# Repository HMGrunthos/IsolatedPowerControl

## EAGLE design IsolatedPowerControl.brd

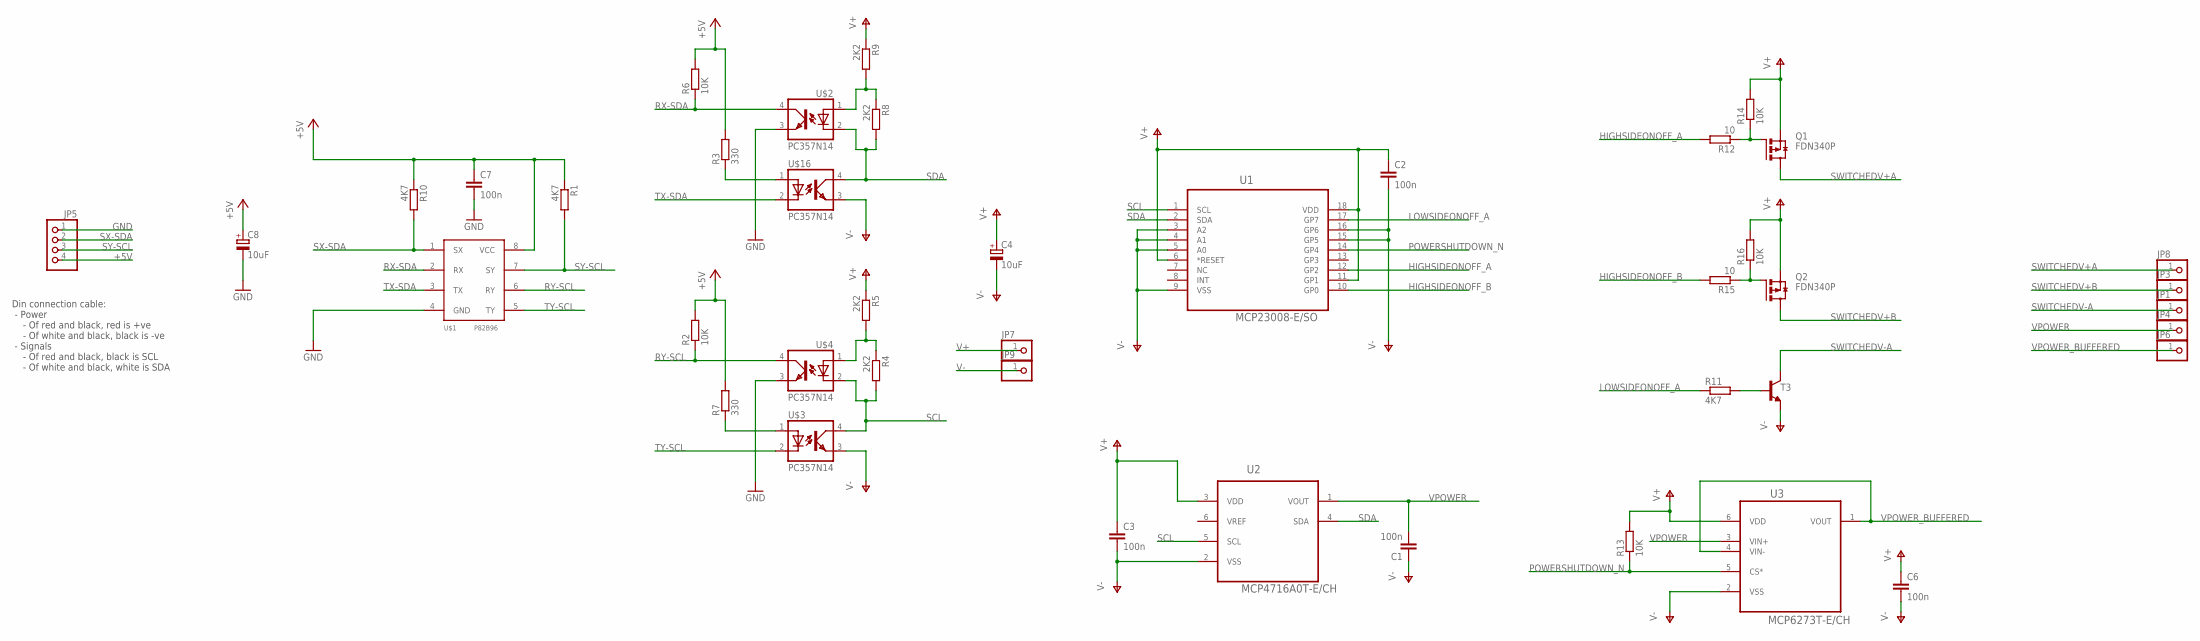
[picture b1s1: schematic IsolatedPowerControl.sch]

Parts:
C1, C2, C3, C6, C7: 100n; C1206K
C4, C8: 10uF; E2-5
JP1, JP3, JP4, JP6, JP7, JP8, JP9: PINHD-1X1LARGEPAD; 1X01-LARGEPAD
JP5: PINHD-1X4; 1X04
Q1, Q2: FDN340P; SUPER-SOT3
R1, R10, R11: 4K7; R0402
R2, R6, R13, R14, R16: 10K; R0805
R3, R7: 330; R0402
R4, R5, R8, R9: 2K2; R0402
R12, R15: 10; R0603
T3: MMBTA42LT1-NPN-SOT23-BEC; SOT23-BEC
U1: MCP23008-E/SO; SOIC127P1030X265-18N
U2: MCP4716A0T-E/CH; SOT95P270X145-6N
U3: MCP6273T-E/CH; SOT95P280X145-6N
U$1: P82B96; SOIC8
U$2, U$3, U$4, U$16: PC357N14; MINI-FLAT-4-DS

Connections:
+5V: C7.1, C8.+, JP5.4, R1.1, R2.2, R3.2, R6.2, R7.2, R10.1, U$1.8 (VCC)
GND: C7.2, C8.-, JP5.1, U$1.4 (GND), U$2.3 (EMIT), U$4.3 (EMIT)
HIGHSIDEONOFF_A: R12.2, U1.12 (GP2)
HIGHSIDEONOFF_B: R15.2, U1.10 (GP0)
LOWSIDEONOFF_A: R11.1, U1.17 (GP7)
unnamed: R3.1, U$16.1 (A)
unnamed: R8.1, R9.2, U$2.1 (A)
unnamed: R7.1, U$3.1 (A)
unnamed: R4.1, R5.2, U$4.1 (A)
unnamed: R11.2, T3.B
unnamed: Q2.1 (G), R15.1, R16.1
unnamed: Q1.1 (G), R12.1, R14.1
POWERSHUTDOWN_N: R13.1, U1.14 (GP4), U3.5 (CS*)
RX-SDA: R6.1, U$1.2 (RX), U$2.4 (COL)
RY-SCL: R2.1, U$1.6 (RY), U$4.4 (COL)
SCL: R4.2, U1.1 (SCL), U2.5 (SCL), U$3.4 (COL), U$4.2 (C)
SDA: R8.2, U1.2 (SDA), U2.4 (SDA), U$2.2 (C), U$16.4 (COL)
SWITCHEDV+A: JP8.1, Q1.3 (D)
SWITCHEDV+B: JP3.1, Q2.3 (D)
SWITCHEDV-A: JP1.1, T3.C
SX-SDA: JP5.2, R10.2, U$1.1 (SX)
SY-SCL: JP5.3, R1.2, U$1.7 (SY)
TX-SDA: U$1.3 (TX), U$16.2 (C)
TY-SCL: U$1.5 (TY), U$3.2 (C)
V+: C2.1, C3.1, C4.+, C6.1, JP7.1, Q1.2 (S), Q2.2 (S), R5.1, R9.1, R13.2, R14.2, R16.2, U1.6 (*RESET), U1.11 (GP1), U1.18 (VDD), U2.3 (VDD), U3.6 (VDD)
V-: C1.1, C2.2, C3.2, C4.-, C6.2, JP9.1, T3.E, U1.3 (A2), U1.4 (A1), U1.5 (A0), U1.9 (VSS), U1.15 (GP5), U1.16 (GP6), U2.2 (VSS), U3.2 (VSS), U$3.3 (EMIT), U$16.3 (EMIT)
VPOWER: C1.2, JP4.1, U2.1 (VOUT), U3.3 (VIN+)
VPOWER_BUFFERED: JP6.1, U3.1 (VOUT), U3.4 (VIN-)

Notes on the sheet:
Din connection cable: - Power - Of red and black, red is +ve - Of white and black, black is -ve - Signals - Of red and black, black is SCL - Of white and black, white is SDA

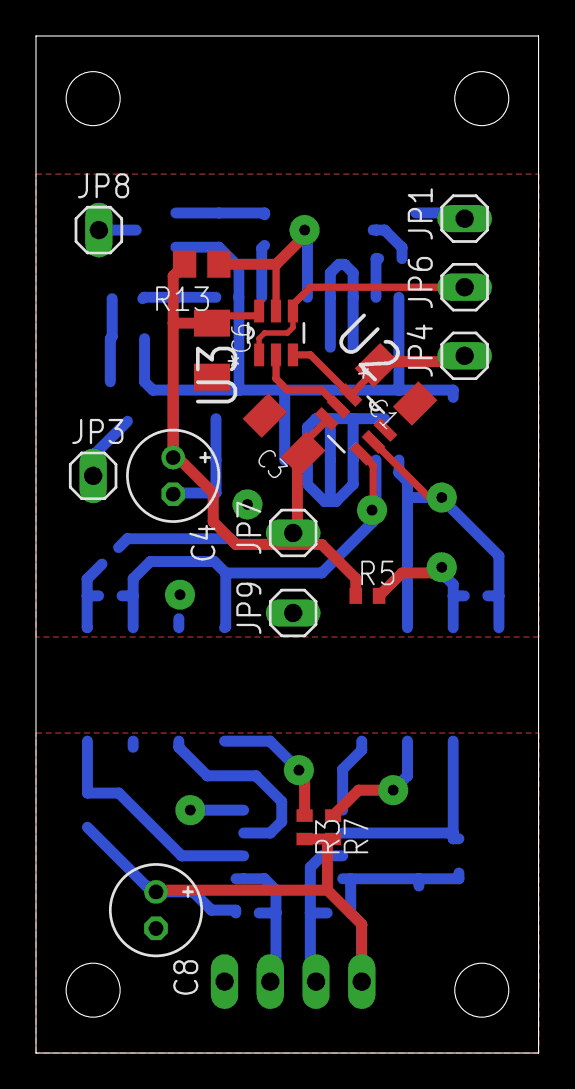
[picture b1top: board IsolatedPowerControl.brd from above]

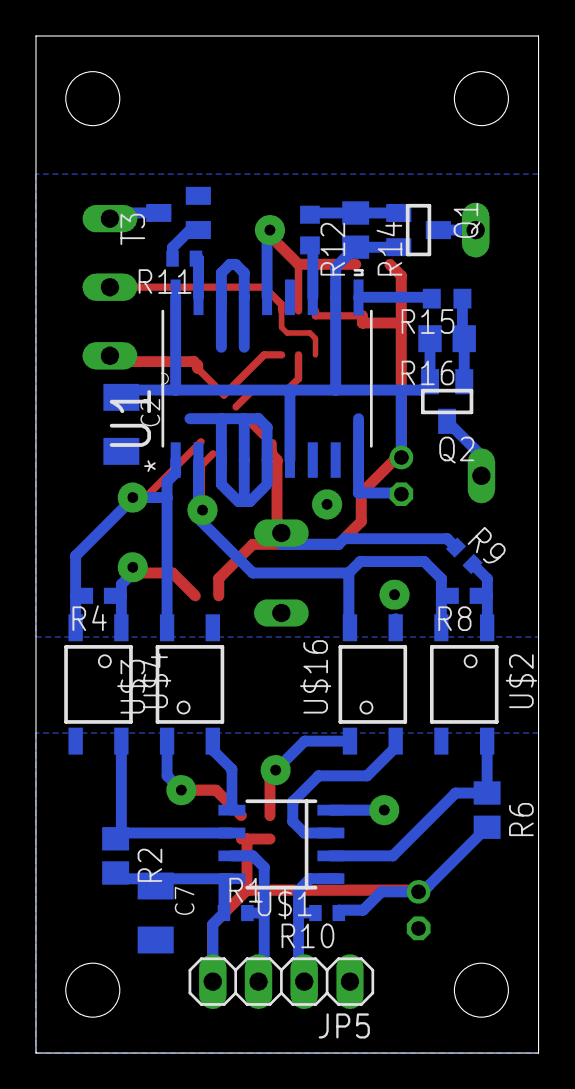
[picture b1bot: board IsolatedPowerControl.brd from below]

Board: 2 copper layers, 27.9 x 56.5 mm, 42 parts (24 on the bottom side), 28 nets.

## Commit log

2018-10-03 Initial checkin
2018-10-03 Initial fit (incomplete routing)
2018-10-04 First layout complete and checked
2018-10-04 Added op amp with enable/power down (MCP6273T) and re-routed.
2018-10-05 Added another isolated aux channel
2018-10-05 Another reroute!
2018-10-05 Increased track width
2018-10-05 Added pdfs of the copper and mask layers
2018-10-06 Tweaks following etching to open up clearances
2018-10-08 Added test software
2018-10-11 Added documentation to schematic. Added STM32 test sketch
2018-10-11 Fixed an error in the cable colour note
2018-10-13 Tested the control board with the cooker. It works!
2018-10-13 Added STM32 variant for the ETARM-STAMP-STM32 and ported over the cooker control sketch
2018-10-14 Minor tweaks to the layout to line things up
2018-10-19 Added sketch that measures and displays temperatures using PT100 probes (just calibrated at 0C tripple point)
2018-10-23 Added sketch to both read temperature and controll the cooker (tested, no link between the two.)
2018-10-23 Added simple IIR filter to temperature channels
2018-10-26 Fixed the flickering vfd. Made the RTD read at 50Hz. Added LED power level indication.
2018-10-27 Added alpha beta filter to the temperature measurements. Still to do (apart from lots of tidying), fix missed temperature readings (while communicating with the hob controller) - look into interrupts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
2018-10-27 Added interrupt to sense new readings from the RTD interface. Added ring buffer to communicate from interrupt to main loop. Moved PID computation into cooker control function. Had a look at ferrites,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
2018-10-27 Added in configuration for GPIO drive strength on the I2C lines
2018-10-28 Fixed the gpio programming to limit the slew rate - sadly it doesn't seem to work on I2C configured pins.
2018-10-29 Added watchdog (and a pin that signals reset.) Added code to recover I2C clock settings when the I2C transaction fails.
2018-10-29 Added minor comment and disabled power control.
2018-10-30 Switched the I2C2 cooker control over to software i2c control, this seems to have resolved the hangup. Made the power level a bit more linear.
2018-11-01 Fixed a bug with string parsing (insufficient space for null terminator.) Introduced rolling display. Hacked in connection tester to run overnight.
2018-11-01 Added photos of the internals of the CE208. Also includes photos of the interface board and it's connections to the hob.
